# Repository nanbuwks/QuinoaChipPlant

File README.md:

# QuinoaChipPlant

キヌアの育種のために、撒種→結実を速いサイクルで回すためのプラントです。

## キヌアとは

キヌア（ Quinua ):南米で食されている雑穀。
栄養的に優れていて、スーパーフードとして注目されている。
乾燥/湿地、低温、塩地などの他の作物が育たない環境でも栽培ができる。
遺伝子が多様で、品種改良が期待される。

## このプラントの目的

1つのチップに1粒ずつ撒種し、水耕栽培を行います。
1つのラックにチップが24収納できますが、チップ1つ分はセンサーのために使うので1つのラックで23粒を撒きます。
芽が出たら1つのラックに10程度に間引きします。
100ラックで実験するとなると、1000株を育成することになります。
収量を目的とするのではなく、促成で種を回収することを目的としています。

# 育成ロボット

水換え、光照射、センサ接続ができるロボットボードです。
1000株分を育成するのは水替えも大変なので、自動で水換えを行います。
プログラムで自動運転できるので、一時冠水を繰り返すような運転を行うことができます。

## 組み立て方、使い方

「キヌア栽培のための制御回路をつくってみよう」
https://qiita.com/nanbuwks/items/138a8bbda59f0657b9df

## 開発コミュニティ

discord OpenHardTerrace 中の #chipplant で開発しています。
https://discord.gg/T8mKzFyu6m

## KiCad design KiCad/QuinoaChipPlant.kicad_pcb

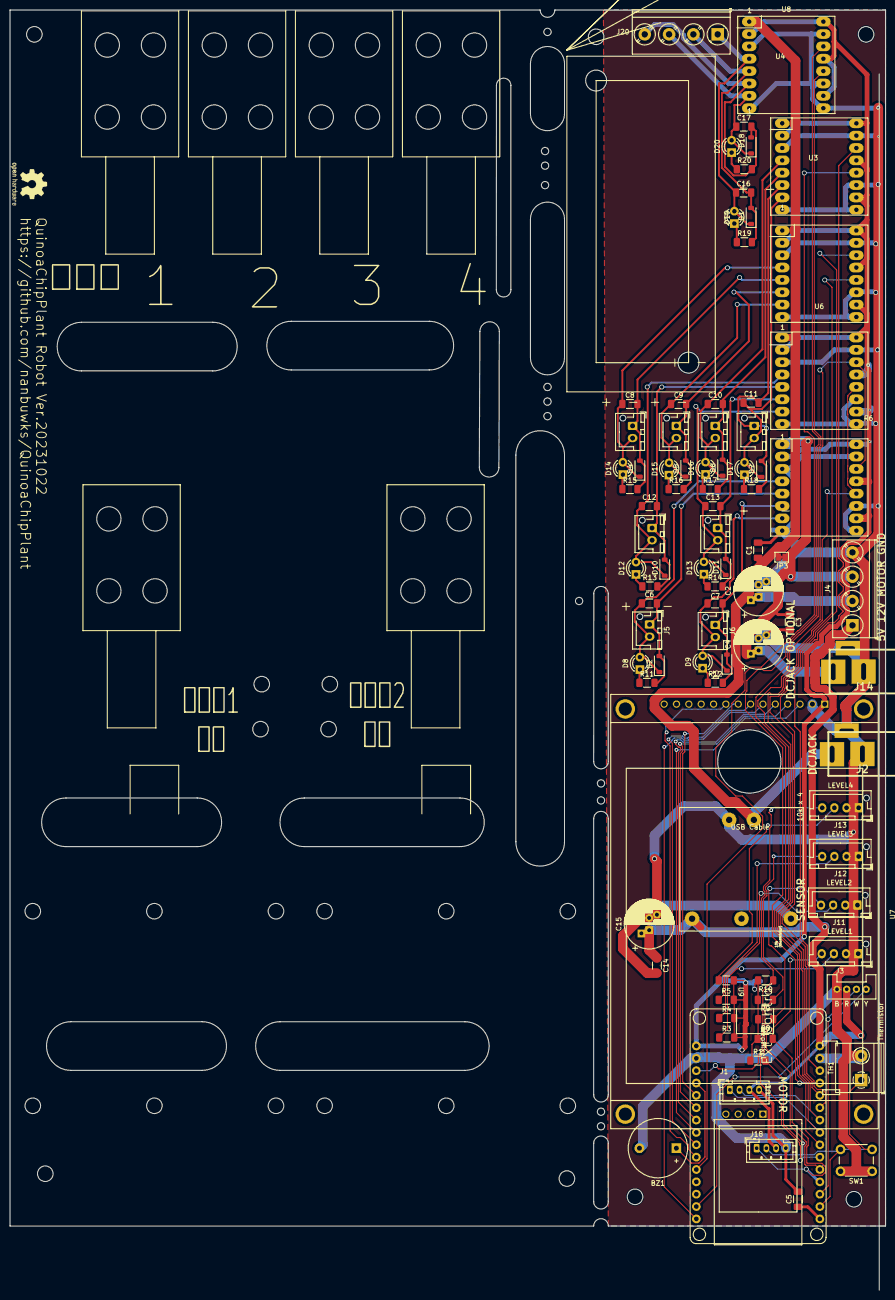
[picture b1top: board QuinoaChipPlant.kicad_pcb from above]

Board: 2 copper layers, 180.0 x 263.2 mm, 138 parts (0 on the bottom side), 63 nets.

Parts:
BZ1: Buzzer; Buzzer_12x9.5RM7.6
C1, C3: C; C_1206_3216Metric_Pad1.33x1.80mm_HandSolder
C2, C4, C15: C_Polarized; CP_Radial_D10.0mm_P2.50mm_P5.00mm
C5: 0.1uF; C_1206_3216Metric_Pad1.33x1.80mm_HandSolder
C6, C7, C8, C9, C10, C11, C12, C13, C14, C16, C17: C; R_1206_3216Metric_Pad1.30x1.75mm_HandSolder
D1, D2, D3, D4, D5, D6, D7, D10, D11, D18: D; D_SOD-123
D8, D9, D12, D13, D14, D15, D16, D17, D19, D20: LED; LED_D3.0mm
J1, J18: GROVE; JST_PH_B4B-PH-K_1x04_P2.00mm_Vertical
J2: DCJACK
J3: LEVEL1; JST_XH_B4B-XH-AM_1x04_P2.50mm_Vertical
J4, J20: Screw_Terminal_01x04; TerminalBlock_Phoenix_PT-1,5-4-5.0-H_1x04_P5.00mm_Horizontal
J5, J6: MOTOR; JST_XH_B2B-XH-AM_1x02_P2.50mm_Vertical
J7, J8, J9, J10, J15, J16: BULB; JST_XH_B2B-XH-AM_1x02_P2.50mm_Vertical
J11: LEVEL2; JST_XH_B4B-XH-AM_1x04_P2.50mm_Vertical
J12: LEVEL3; JST_XH_B4B-XH-AM_1x04_P2.50mm_Vertical
J13: LEVEL4; JST_XH_B4B-XH-AM_1x04_P2.50mm_Vertical
J14: DCJACK OPTIONAL; DCJACK
JP3: SolderJumper_2_Bridged; SolderJumper-2_P1.3mm_Bridged_Pad1.0x1.5mm
R1: R; R_1206_3216Metric_Pad1.30x1.75mm_HandSolder
R3, R4, R5, R6, R11, R12, R13, R14, R15, R16, R17, R18, R19, R20: 470; R_1206_3216Metric_Pad1.30x1.75mm_HandSolder
R7, R8, R9, R10: 10K; R_1206_3216Metric_Pad1.30x1.75mm_HandSolder
REF07, REF09: MountingHole_4.3mm_M4_DIN965
REF08, REF08#2, REF10, REF11, REF12, REF12#2, REF12#3, REF13, REF14, REF15, REF16, REF17, REF18, REF19, REF21, REF22, REF23, REF24, REF26, REF27, REF100, REF111, REF112, REF113, REF114, REF115, REF116, REF117, REF119, REF120, REF121, REF122, REF123, REF124, REF125, REF126, REF127, REF128, REF129, REF130, REF131, REF132, REF133, REF134, REF140, REF141, REF230: MountingHole_3.2mm_M3
REF118: OSHW-Logo2_9.8x8mm_SilkScreen
SW1: SW_Push; SW_PUSH_6mm
TH1: Thermistor; TerminalBlock_Phoenix_MKDS-1,5-2_1x02_P5.00mm_Horizontal
U1: ESP32_DEVKIT_V1
U2, U3, U4, U6, U8: SparkFun_TB6612FNG_MOTOR_DRIVER_MODULE
U5: SEEED_GROVE; Seeedstudio_Grove_110990030_Vertical_4pin_2mmpitch
U7: CR2013-MI2120; TFT3.2_ILI9341
U9: YRB_YMD-10WR3_YRA_YMD-10WR3
USB Cable: MountingHole_8.4mm_M8

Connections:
+3V3: R1.1, R3.2, R4.2, R5.2, R6.2, R7.1, R8.2, R9.2, R10.2, U1.16 (3V3), U2.2 (VCC), U2.10 (PWMB), U2.13 (STBY), U2.16 (PWMA), U3.2 (VCC), U3.10 (PWMB), U3.13 (STBY), U3.16 (PWMA), U4.2 (VCC), U4.10 (PWMB), U4.13 (STBY), U4.16 (PWMA), U6.2 (VCC), U6.10 (PWMB), U6.13 (STBY), U6.16 (PWMA), U7.1 (VCC), U8.2 (VCC), U8.10 (PWMB), U8.13 (STBY), U8.16 (PWMA)
+5V: C14.1, C15.1, J1.3, J4.1, J18.3, U1.15 (VIN), U5.3 (Red/VCC), U9.3 (+Vo)
+12V: C1.1, C2.1, J2.1, J4.2, JP3.2 (B), U3.1 (VM), U4.1 (VM), U6.1 (VM), U8.1 (VM), U9.1 (-Vin)
+12VA: C3.1, C4.1, J4.3, J14.1, JP3.1 (A), U2.1 (VM)
BULB1: U1.10 (27), U3.14 (AI1)
BULB2: U1.11 (14), U3.12 (BI1)
BULB3: U1.13, U4.14 (AI1)
BULB4: U1.26 (21), U4.12 (BI1)
GND: BZ1.2 (+), C1.2, C2.2, C3.2, C4.2, C5.2, C14.2, C15.2, J1.4, J2.2, J2.3, J3.1, J3.2, J4.4, J11.1, J11.2, J12.1, J12.2, J13.1, J13.2, J14.2, J14.3, J18.4, SW1.1, TH1.2, U1.14 (GND), U1.17 (GND), U2.3 (GND), U2.8 (GND), U2.9 (GND), U2.11 (BI2), U2.15 (AI2), U3.3 (GND), U3.8 (GND), U3.9 (GND), U3.11 (BI2), U3.15 (AI2), U4.3 (GND), U4.8 (GND), U4.9 (GND), U4.11 (BI2), U4.15 (AI2), U5.4 (Black/GND), U6.3 (GND), U6.8 (GND), U6.9 (GND), U6.11 (BI2), U6.15 (AI2), U7.2 (GND), U8.3 (GND), U8.8 (GND), U8.9 (GND), U8.11 (BI2), U8.15 (AI2), U9.2 (+Vin), U9.5 (0V/-Vo)
GROVE1: U1.29 (22), U5.1 (Yellow/Dn/An/RX/SCL)
GROVE2: U1.3 (VN), U5.2 (White/Dn1/An1/TX/SDA)
MOTOR1: J1.1, U1.8 (25), U2.14 (AI1), U6.14 (AI1)
MOTOR2: J1.2, U1.9 (26), U2.12 (BI1), U6.12 (BI1)
unnamed: BZ1.1 (-), U1.19 (2)
unnamed: C16.2, D1.2 (A), J20.2, R19.2, U8.5 (A02)
unnamed: C16.1, D1.1 (K), D19.2 (A), J20.1, U8.4 (A01)
unnamed: C6.2, D2.2 (A), J5.1, R11.2, U2.5 (A02)
unnamed: C6.1, D2.1 (K), D8.2 (A), J5.2, U2.4 (A01)
unnamed: C7.2, D3.2 (A), J6.1, R12.2, U2.6 (B02)
unnamed: C7.1, D3.1 (K), D9.2 (A), J6.2, U2.7 (B01)
unnamed: C8.2, D4.2 (A), J9.1, R15.2, U3.5 (A02)
unnamed: C9.2, D5.2 (A), J10.1, R16.2, U3.6 (B02)
unnamed: C10.2, D6.2 (A), J15.1, R17.2, U4.5 (A02)
unnamed: C11.2, D7.2 (A), J16.1, R18.2, U4.6 (B02)
unnamed: D8.1 (K), R11.1
unnamed: D9.1 (K), R12.1
unnamed: C12.2, D10.2 (A), J7.1, R13.2, U6.5 (A02)
unnamed: C12.1, D10.1 (K), D12.2 (A), J7.2, U6.4 (A01)
unnamed: C13.2, D11.2 (A), J8.1, R14.2, U6.6 (B02)
unnamed: C13.1, D11.1 (K), D13.2 (A), J8.2, U6.7 (B01)
unnamed: D12.1 (K), R13.1
unnamed: D13.1 (K), R14.1
unnamed: C8.1, D4.1 (K), D14.2 (A), J9.2, U3.4 (A01)
unnamed: D14.1 (K), R15.1
unnamed: C9.1, D5.1 (K), D15.2 (A), J10.2, U3.7 (B01)
unnamed: D15.1 (K), R16.1
unnamed: C10.1, D6.1 (K), D16.2 (A), J15.2, U4.4 (A01)
unnamed: D16.1 (K), R17.1
unnamed: C11.1, D7.1 (K), D17.2 (A), J16.2, U4.7 (B01)
unnamed: D17.1 (K), R18.1
unnamed: C17.2, D18.2 (A), J20.4, R20.2, U8.6 (B02)
unnamed: C17.1, D18.1 (K), D20.2 (A), J20.3, U8.7 (B01)
unnamed: D19.1 (K), R19.1
unnamed: D20.1 (K), R20.1
unnamed: J3.3, R3.1
unnamed: J11.3, R4.1
unnamed: J12.3, R5.1
unnamed: J13.3, R6.1
unnamed: U1.20 (4), U7.8 (LED)
unnamed: U1.23 (5), U7.3 (~CS)
unnamed: U1.21 (16), U7.4 (RESET)
unnamed: U1.22 (17), U7.5 (D/~C)
unnamed: U1.24 (18), U7.7 (SCK)
unnamed: U1.25 (19), U7.9 (MISO)
unnamed: U1.30 (23), U7.6 (MOSI)
unnamed: C5.1, U1.1 (EN)
RELAY1: U1.12, U8.14 (AI1)
RELAY2: U1.7 (33), U8.12 (BI1)
SW_THERMISTOR: J18.2, R1.2, SW1.2, TH1.1, U1.2 (VP)
WATERSENSOR1: J3.4, J18.1, R7.2, U1.4 (34)
WATERSENSOR2: J11.4, R8.1, U1.5 (35)
WATERSENSOR3: J12.4, R9.1, U1.6 (32)
WATERSENSOR4: J13.4, R10.1, U1.18 (15)

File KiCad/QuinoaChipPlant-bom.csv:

"ID";"指定子";"フットプリント";"数量";"名称";"供給業者、参考資料";
1;"U2,U8,U6,U3,U4";"SparkFun_TB6612FNG_MOTOR_DRIVER_MODULE";5;"SparkFun_TB6612FNG_MOTOR_DRIVER_MODULE";;;
2;"J11";"JST_XH_B4B-XH-AM_1x04_P2.50mm_Vertical";1;"LEVEL2";;;
3;"J7,J10,J16,J9,J15,J8";"JST_XH_B2B-XH-AM_1x02_P2.50mm_Vertical";6;"BULB";;;
4;"D1,D4,D18,D3,D5,D7,D2,D11,D6,D10";"D_SOD-123";10;"D";;;
5;"R10,R8,R9,R7";"R_1206_3216Metric_Pad1.30x1.75mm_HandSolder";4;"10K";;;
6;"R16,R6,R15,R13,R14,R3,R17,R4,R12,R11,R5,R19,R20,R18";"R_1206_3216Metric_Pad1.30x1.75mm_HandSolder";14;"470";;;
7;",,,,,,,";"";8;"";;;
8;"U5";"Seeedstudio_Grove_110990030_Vertical_4pin_2mmpitch";1;"SEEED_GROVE";;;
9;"J6,J5";"JST_XH_B2B-XH-AM_1x02_P2.50mm_Vertical";2;"MOTOR";;;
10;"D8,D9,D16,D15,D17,D14,D20,D13,D19,D12";"LED_D3.0mm";10;"LED";;;
11;"J4,J20";"TerminalBlock_Phoenix_PT-1,5-4-5.0-H_1x04_P5.00mm_Horizontal";2;"Screw_Terminal_01x04";;;
12;"U9";"YRB_YMD-10WR3_YRA_YMD-10WR3";1;"~";;;
13;"C5";"C_1206_3216Metric_Pad1.33x1.80mm_HandSolder";1;"0.1uF";;;
14;"BZ1";"Buzzer_12x9.5RM7.6";1;"Buzzer";;;
15;"C7,C9,C8,C14,C6,C16,C17,C10,C11,C12,C13";"R_1206_3216Metric_Pad1.30x1.75mm_HandSolder";11;"C";;;
16;"C3,C1";"C_1206_3216Metric_Pad1.33x1.80mm_HandSolder";2;"C";;;
17;"J13";"JST_XH_B4B-XH-AM_1x04_P2.50mm_Vertical";1;"LEVEL4";;;
18;"U1";"ESP32_DEVKIT_V1";1;"ESP32_DEVKIT_V1";;;
19;"J3";"JST_XH_B4B-XH-AM_1x04_P2.50mm_Vertical";1;"LEVEL1";;;
20;"C2,C4,C15";"CP_Radial_D10.0mm_P2.50mm_P5.00mm";3;"C_Polarized";;;
21;"J18,J1";"JST_PH_B4B-PH-K_1x04_P2.00mm_Vertical";2;"GROVE";;;
22;"J2";"DCJACK";1;"DCJACK";;;
23;"TH1";"TerminalBlock_Phoenix_MKDS-1,5-2_1x02_P5.00mm_Horizontal";1;"Thermistor";;;
24;"J14";"DCJACK";1;"DCJACK OPTIONAL";;;
25;"U7";"TFT3.2_ILI9341";1;"CR2013-MI2120";;;
26;"SW1";"SW_PUSH_6mm";1;"SW_Push";;;
27;"J12";"JST_XH_B4B-XH-AM_1x04_P2.50mm_Vertical";1;"LEVEL3";;;
28;"R1";"R_1206_3216Metric_Pad1.30x1.75mm_HandSolder";1;"R";;;
29;"JP3";"SolderJumper-2_P1.3mm_Bridged_Pad1.0x1.5mm";1;"SolderJumper_2_Bridged";;;

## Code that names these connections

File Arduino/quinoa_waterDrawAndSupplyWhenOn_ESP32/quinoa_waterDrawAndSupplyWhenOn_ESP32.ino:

/* Version 202304
#define PUMP0_PIN 27
#define PUMP1_PIN 26
#define FAN_PIN 22
#define BEEP_PIN 2
#define WATERSENSOR_PIN 25
#define BEEP
*/


/* Version 202304 */
#define PUMP0_PIN 25
#define PUMP1_PIN 26
#define BULB0_PIN 27
#define BULB1_PIN 14
#define BULB2_PIN 13
#define BULB3_PIN 21
#define GROVE0_PIN 22
#define GROVE1_PIN 39         // VN input only
#define BEEP_PIN 2
#define WATERSENSOR0_PIN 34
#define WATERSENSOR0_PIN 35
#define WATERSENSOR0_PIN 32
#define WATERSENSOR0_PIN 33   
#define BEEP
#define SW_THERMISTOR_PIN A0  // VP input only

void beep(int millis) {
  Serial.printf("beep:%d", millis);
#ifdef BEEP
  digitalWrite(BEEP_PIN, HIGH);
#endif
  delay(millis);
  digitalWrite(BEEP_PIN, LOW);
}
void pi() {
  beep(200);
}
void pipi() {
  beep(200);
  delay(50);
  beep(100);

}
void pipipipi() {
  beep(200);
  delay(50);
  beep(100);
  delay(100);
  beep(100);
  delay(100);
  beep(100);

}
void peee() {
  beep(1000);
}


void runPUMP0() {
  digitalWrite(PUMP0_PIN, HIGH);
}
void stopPUMP0() {
  digitalWrite(PUMP0_PIN, LOW);
}
//------------------------------------------------------------------------------
void setup() {

  Serial.begin(115200);
  delay(100);
  Serial.println("WATERCONTROLLER START");
  pinMode(WATERSENSOR_PIN, INPUT_PULLUP);
  pinMode(PUMP0_PIN, OUTPUT);
  pinMode(PUMP1_PIN, OUTPUT);
  pinMode(BEEP_PIN, OUTPUT);
  digitalWrite(PUMP0_PIN, 0);
  digitalWrite(PUMP1_PIN, 0);
  digitalWrite(FAN_PIN, 0);
  digitalWrite(BEEP_PIN, 0);
  pipi();
  Serial.println( digitalRead(WATERSENSOR_PIN));
  // 5分排水
  Serial.println("排水");
  digitalWrite(PUMP0_PIN, 1);
  delay(300000);
  digitalWrite(PUMP0_PIN, 0);

  
}

void loop()
{
    // 給水
  while ( 1 == digitalRead(WATERSENSOR_PIN )){
    Serial.println("給水");
    digitalWrite(PUMP1_PIN, 1);
    while ( 1 == digitalRead(WATERSENSOR_PIN )){
      delay(1000);
  }}
  while ( 0 == digitalRead(WATERSENSOR_PIN )){
    Serial.println("完了");
    digitalWrite(PUMP1_PIN, 0);
    while ( 0 == digitalRead(WATERSENSOR_PIN )){
      delay(1000);
  }}
  delay(1000);
}     

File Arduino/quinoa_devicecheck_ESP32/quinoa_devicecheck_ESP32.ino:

/* Version 202304
#define PUMP0_PIN 27
#define PUMP1_PIN 26
#define FAN_PIN 22
#define BEEP_PIN 2
#define WATERSENSOR_PIN 25
#define BEEP
*/


/* Version 202304 */
#define PUMP0_PIN 25
#define PUMP1_PIN 26
#define VALVE0_PIN 27
#define VALVE1_PIN 14
#define VALVE2_PIN 13
#define VALVE3_PIN 21
#define GROVE0_PIN 22
#define GROVE1_PIN 39         // VN input only
#define BEEP_PIN 2
#define WATERSENSOR0_PIN 34
#define WATERSENSOR1_PIN 35
#define WATERSENSOR2_PIN 32
#define WATERSENSOR3_PIN 33   
#define BEEP
#define SW_THERMISTOR_PIN A0  // VP input only
\
//------------------------------------------------------------------------------
void setup() {

  Serial.begin(115200);
  delay(100);
  Serial.println("WATERCONTROLLER START");
  pinMode(WATERSENSOR0_PIN, INPUT);
  pinMode(WATERSENSOR1_PIN, INPUT);
  pinMode(WATERSENSOR2_PIN, INPUT);
  pinMode(WATERSENSOR3_PIN, INPUT);
  pinMode(PUMP0_PIN, OUTPUT);
  pinMode(PUMP1_PIN, OUTPUT);
  pinMode(BEEP_PIN, OUTPUT);
  pinMode(VALVE0_PIN, OUTPUT);
  pinMode(VALVE1_PIN, OUTPUT);
  pinMode(VALVE2_PIN, OUTPUT);
  pinMode(VALVE3_PIN, OUTPUT);
  digitalWrite(PUMP0_PIN, 0);
  digitalWrite(PUMP1_PIN, 0);
  digitalWrite(BEEP_PIN, 0);
  digitalWrite(VALVE0_PIN, 0);
  digitalWrite(VALVE1_PIN, 0);
  digitalWrite(VALVE2_PIN, 0);
  digitalWrite(VALVE3_PIN, 0);

  
}

void loop()
{
 
  Serial.printf("WATERSENSOR0:%d\n",digitalRead(WATERSENSOR0_PIN ));
  Serial.printf("WATERSENSOR1:%d\n",digitalRead(WATERSENSOR1_PIN ));
  Serial.printf("WATERSENSOR2:%d\n",digitalRead(WATERSENSOR2_PIN ));
  Serial.printf("WATERSENSOR3:%d\n",digitalRead(WATERSENSOR3_PIN ));
  Serial.printf("BEEP\n");
  digitalWrite(BEEP_PIN, 1);
  delay(1000);
  digitalWrite(BEEP_PIN, 0);
  delay(1000);
  Serial.printf("PUMP0\n");
  digitalWrite(PUMP0_PIN, 1);
  delay(1000);
  digitalWrite(PUMP0_PIN, 0);
  delay(1000);
  Serial.printf("PUMP1\n");
  digitalWrite(PUMP1_PIN, 1);
  delay(1000);
  digitalWrite(PUMP1_PIN, 0);
  delay(1000);
  Serial.printf("VALVE0\n");
  digitalWrite(VALVE0_PIN, 1);
  delay(1000);
  digitalWrite(VALVE0_PIN, 0);
  delay(1000);
  Serial.printf("VALVE1\n");
  digitalWrite(VALVE1_PIN, 1);
  delay(1000);
  digitalWrite(VALVE1_PIN, 0);
  delay(1000);
  Serial.printf("VALVE2\n");
  digitalWrite(VALVE2_PIN, 1);
  delay(1000);
  digitalWrite(VALVE2_PIN, 0);
  delay(1000);
  Serial.printf("VALVE3\n");
  digitalWrite(VALVE3_PIN, 1);
  delay(1000);
  digitalWrite(VALVE3_PIN, 0);
  delay(1000);
  
  
  
}     

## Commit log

2023-03-23 modify README
2023-05-08 import KiCad file from IoTHandyFan
2023-05-08 mv KiCad file from IoTHandyFan
2023-05-08 changename KiCad files.
2023-05-08 change to KiCad 7 files from KiCad 5 files.
2023-05-10 make pump, bulb , sensor PCB.
2023-05-10 PCB release 20230510 Version.
2023-05-21 Add esp32 sketchc
2023-05-21 Add LGT8F328 sketch
2023-06-04 update LGT8F328 sketch
2023-07-08 modify arduino sketch
2023-09-01 202305 version
2023-09-01 add devicecheck program
2023-09-02 add images
2023-09-26 Ver.20230911
2025-03-05 202311 version
